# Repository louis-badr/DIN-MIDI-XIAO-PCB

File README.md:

# DIN-MIDI-XIAO-PCB

<div>

</div>

DIN MIDI PCB for Seeed Studio XIAO format boards - designed for CNC milling

Pinout:

-   Pin 1 -> GND
-   Pin 2 -> MIDI- / 5
-   Pin 3 -> MIDI+ / 4
-   Pin 4 -> +5V

Pin 1 and 4 are for powering the XIAO board, only connect them when USB is not.

```c++
#include <HardwareSerial.h>
#include <MIDI.h>

#define MIDI_IN 8 // pin 8 for XIAO ESP32S3 - change to your pin

MIDI_CREATE_INSTANCE(HardwareSerial, Serial1, MIDI)

void setup()
{
    Serial.begin(115200); // for debugging
    Serial1.begin(31250, SERIAL_8N1, MIDI_IN, -1); // for MIDI input
    MIDI.begin(MIDI_CHANNEL_OMNI);
}

void loop()
{
    MIDI.read();
}
```

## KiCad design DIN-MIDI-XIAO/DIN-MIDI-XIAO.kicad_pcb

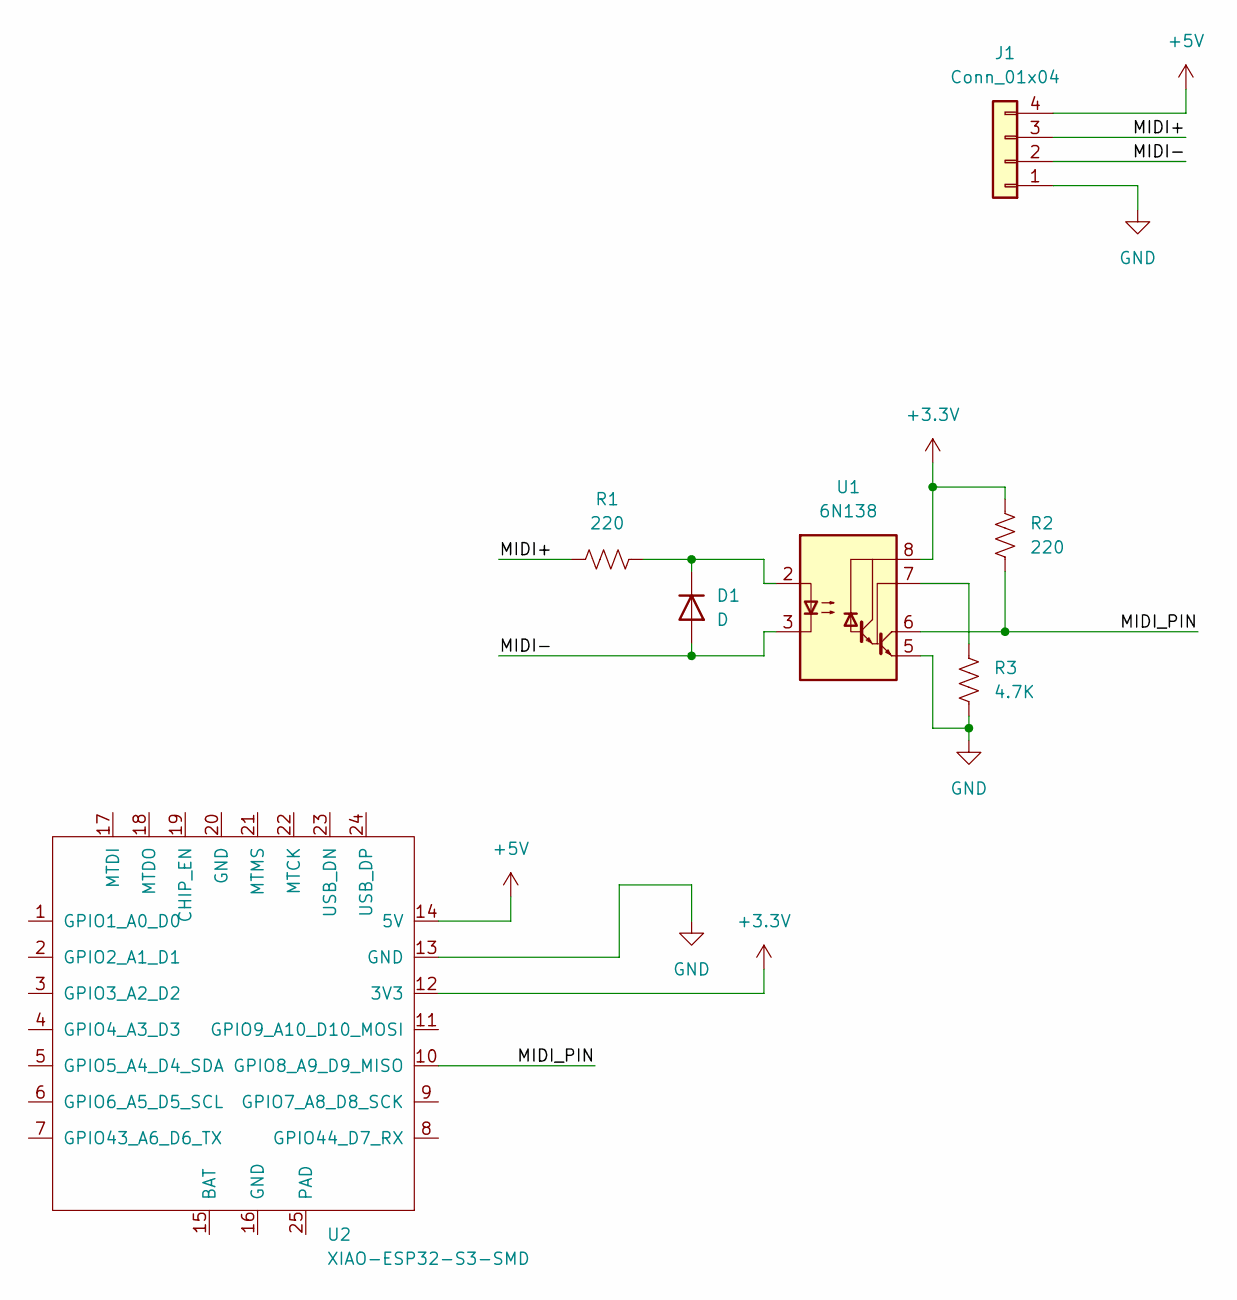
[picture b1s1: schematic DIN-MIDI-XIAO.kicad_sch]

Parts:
D1: D; R_Axial_DIN0207_L6.3mm_D2.5mm_P7.62mm_Horizontal
J1: Conn_01x04; PinHeader_1x04_P2.54mm_Horizontal
R1, R2: 220; R_Axial_DIN0207_L6.3mm_D2.5mm_P7.62mm_Horizontal
R3: 4.7K; R_Axial_DIN0207_L6.3mm_D2.5mm_P7.62mm_Horizontal
U1: 6N138; DIP-8_W7.62mm_Socket_LongPads
U2: XIAO-ESP32-S3-SMD; XIAO-ESP32S3-SMD

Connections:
+3.3V: R2.1, U1.8 (VCC), U2.12 (3V3)
+5V: J1.4, U2.14 (5V)
/MIDI+: J1.3, R1.1
/MIDI-: D1.2 (A), J1.2, U1.3 (C2)
/MIDI_PIN: R2.2, U1.6 (VO2), U2.10 (GPIO8_A9_D9_MISO)
GND: J1.1, R3.2, U1.5 (GND), U2.13 (GND)
unnamed: D1.1 (K), R1.2, U1.2 (C1)
unnamed: R3.1, U1.7 (VO1)

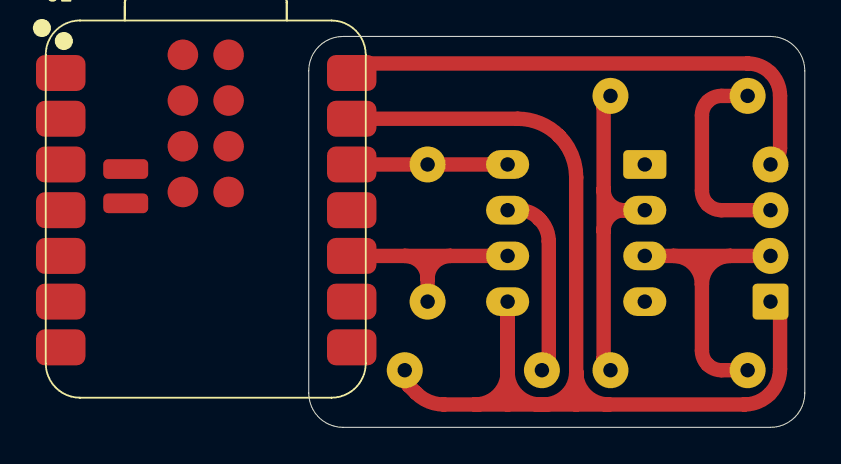
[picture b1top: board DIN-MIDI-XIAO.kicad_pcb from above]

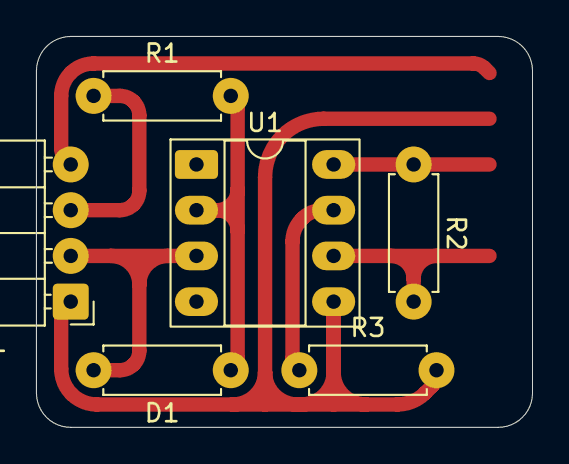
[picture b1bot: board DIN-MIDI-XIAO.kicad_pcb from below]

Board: 2 copper layers, 27.6 x 21.7 mm, 7 parts (6 on the bottom side), 8 nets.

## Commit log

2025-05-12 Fixed pictures
2025-05-12 Added libraries
